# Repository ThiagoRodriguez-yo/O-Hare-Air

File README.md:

O-Hare Air

Sistema automatizado de ventilación controlado por ESP32-C3, equipado con sensor de temperatura y humedad DHT11, pantalla OLED de estado y módulo de relé para control de potencia.

Especificaciones generales:

Dimensiones de la placa / diseño: Adaptado para montaje compacto.

Alimentación: Batería LiPo de 7.4V (2S).

Regulación: Voltaje estabilizado a 5V mediante regulador L7805 con condensadores de filtrado (100nF y 10µF).

Microcontrolador: ESP32-C3 Super Mini.

Componentes pasivos: Resistencias y condensadores en formato SMD 1206, diodo 1N4007 en encapsulado SMA.

Objetivo del proyecto:

El objetivo principal de este proyecto es diseñar e implementar un sistema de ventilación inteligente y automatizado que regule el flujo de aire en función de las condiciones ambientales medidas por sensores, aplicando conocimientos de diseño de circuitos impresos y programación de microcontroladores.

Componentes utilizados:

Microcontrolador: ESP32-C3 Super Mini.

Memoria: 400 KB SRAM, 4 MB Flash. Conectividad: Wi-Fi (2.4 GHz) y Bluetooth 5.0 LE.

Batería LiPo: 7.4V (2 celdas de 3.7V).

Regulador de voltaje: L7805.

Sensor de temperatura y humedad: DHT11.

Pantalla de visualización: Display OLED I2C.

Control de potencia: Módulo de relé.

Control general: Interruptor de palanca y conector de batería.

Protección: Diodo 1N4007 (encapsulado SMA).

Diseño del circuito: 

Descripcion del funcionamiento:

El sistema monitorea constantemente la temperatura y la humedad del ambiente mediante el sensor DHT11. Los valores leídos se procesan en el ESP32-C3 y se visualizan en tiempo real a través de la pantalla OLED. Cuando la temperatura o la humedad superan los umbrales configurados, el microcontrolador activa el módulo de relé para encender el ventilador de forma automática. Todo el sistema es alimentado por una batería LiPo de 7.4V, la cual pasa por un interruptor general y se reduce a 5V limpios mediante el regulador lineal L7805 protegido por condensadores de desacoplamiento.

Esquematico:

Layout de PCB:

Pasos a seguir para armar el proyecto:

1. Preparación de la placa:

Descargar el archivo de diseño de PCB desde el repositorio.

Imprimir el diseño en una hoja fotográfica utilizando impresora láser con tóner.

Transferir el diseño a la placa de cobre mediante calor (planchado).

Revelar y grabar la placa utilizando percloruro férrico hasta eliminar el cobre sobrante.

Perforar los puntos necesarios y limpiar la placa adecuadamente.

2. Soldar los componentes:

Soldar los componentes en el siguiente orden recomendado para mayor comodidad:

Condensadores y resistencias SMD (formato 1206).

Diodo SMA y pines de conexión.

Regulador de voltaje L7805.

Conectores de batería, relé y pantalla.

3. Código y programación

El código establece las instrucciones que ejecutará el ESP32-C3 para leer el sensor DHT11, mostrar la información en la pantalla OLED y accionar el relé del ventilador según corresponda.

Compilación y carga:

Conectar la placa ESP32-C3 Super Mini a un ordenador mediante un cable USB-C.

Abrir el programa Arduino IDE.

Seleccionar la placa ESP32_C3_DEV_MODULE y el puerto USB correspondiente en las herramientas.

Instalar las librerías necesarias para el sensor DHT11 y la pantalla OLED desde el gestor de bibliotecas.

Verificar el código en busca de errores y proceder a subirlo al microcontrolador.

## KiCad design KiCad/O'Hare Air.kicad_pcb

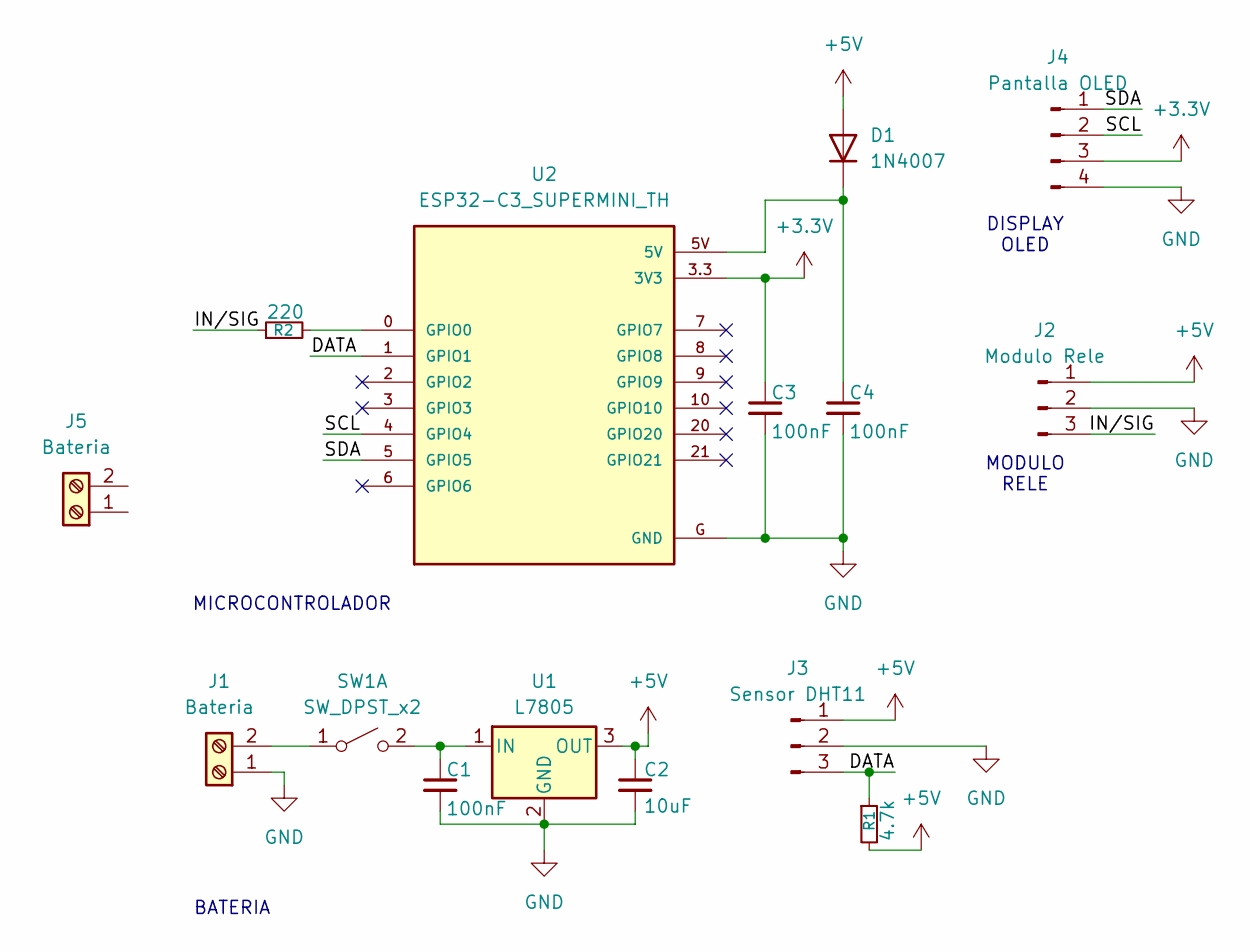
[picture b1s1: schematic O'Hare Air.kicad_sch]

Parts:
C1, C3, C4: 100nF; C_1206_3216Metric
C2: 10uF; C_1206_3216Metric
D1: 1N4007; D_1206_3216Metric
J1: Bateria; XT30 connector
J2: Modulo Rele; PinHeader_1x03_P2.54mm_Vertical
J3: Sensor DHT11; PinHeader_1x03_P2.54mm_Vertical
J4: Pantalla OLED; PinHeader_1x04_P2.54mm_Vertical
J5: Bateria; ohareair
R1: 4.7k; R_1206_3216Metric
R2: 220; R_1206_3216Metric
SW1: SW_DPST_x2; SW_SPDT_TH_Vertical
U1: L7805; PinHeader_1x03_P2.54mm_Vertical
U2: ESP32-C3_SUPERMINI_TH; MODULE_ESP32-C3_SUPERMINI_TH

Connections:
+3.3V: C3.1, J4.3, U2.3.3 (3V3)
+5V: C2.1, D1.2 (A), J2.1, J3.1, R1.2, U1.3 (OUT)
/DATA: J3.3, R1.1, U2.1 (GPIO1)
/IN/SIG: J2.3, R2.1
/SCL: J4.2, U2.4 (GPIO4)
/SDA: J4.1, U2.5 (GPIO5)
GND: C1.2, C2.2, C3.2, C4.2, J1.1, J2.2, J3.2, J4.4, U1.2 (GND), U2.G (GND)
unnamed: C4.1, D1.1 (K), U2.5V
unnamed: J1.2, SW1.1 (A)
unnamed: C1.1, SW1.2 (B), U1.1 (IN)
unnamed: R2.2, U2.0 (GPIO0)

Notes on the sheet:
MICROCONTROLADOR
DISPLAY OLED
BATERIA
MODULO RELE

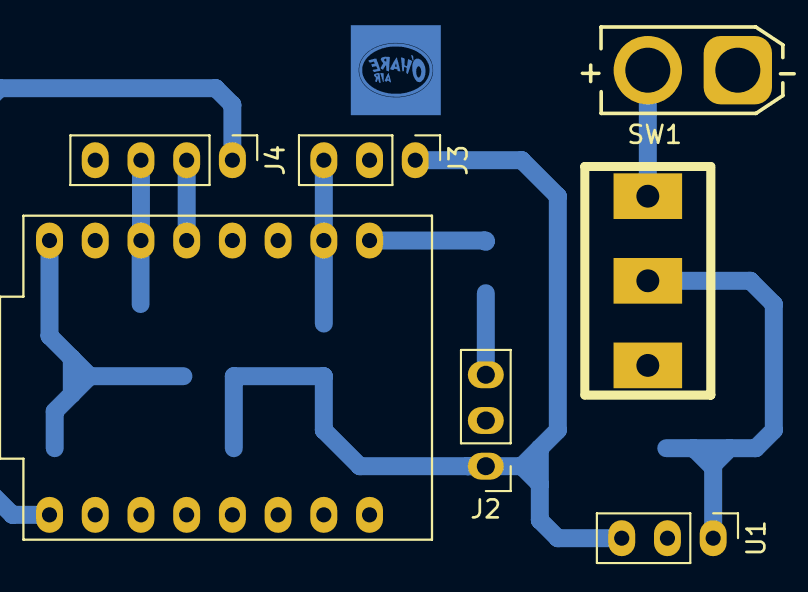
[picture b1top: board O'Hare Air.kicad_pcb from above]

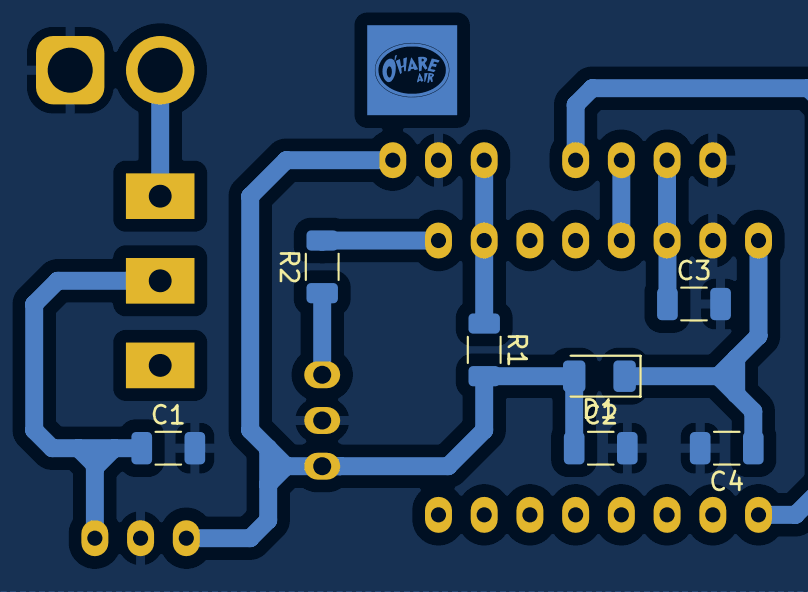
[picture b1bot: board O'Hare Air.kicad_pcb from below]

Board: 2 copper layers, 15 parts (8 on the bottom side), 11 nets.
